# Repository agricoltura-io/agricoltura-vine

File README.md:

# agricoltura-vine
daisy chainable interface for a variety of sensors for various agriculture applications, this is Agricoltura-io's wired sense and control platform.

Quick Specs:
- ST Microelectronics STM32F446RET6 ARM Cortex M4F 180MHZ MCU
- 5V Tolerant Analog Inputs
- 8x I2C interfaces
- 4x UART interface (via mux)
- 8x 5V digital IO ports
- 2x G5LE-14 DC5 SPDT Relays
- USB 2.0 connectivity
- RS485 port
- 24VAC power input
- 2A 3.3V DCDC Regulator, for supporting lots of sensors
- 2A 5V DCDC Regulator, for 5V IO and other devices

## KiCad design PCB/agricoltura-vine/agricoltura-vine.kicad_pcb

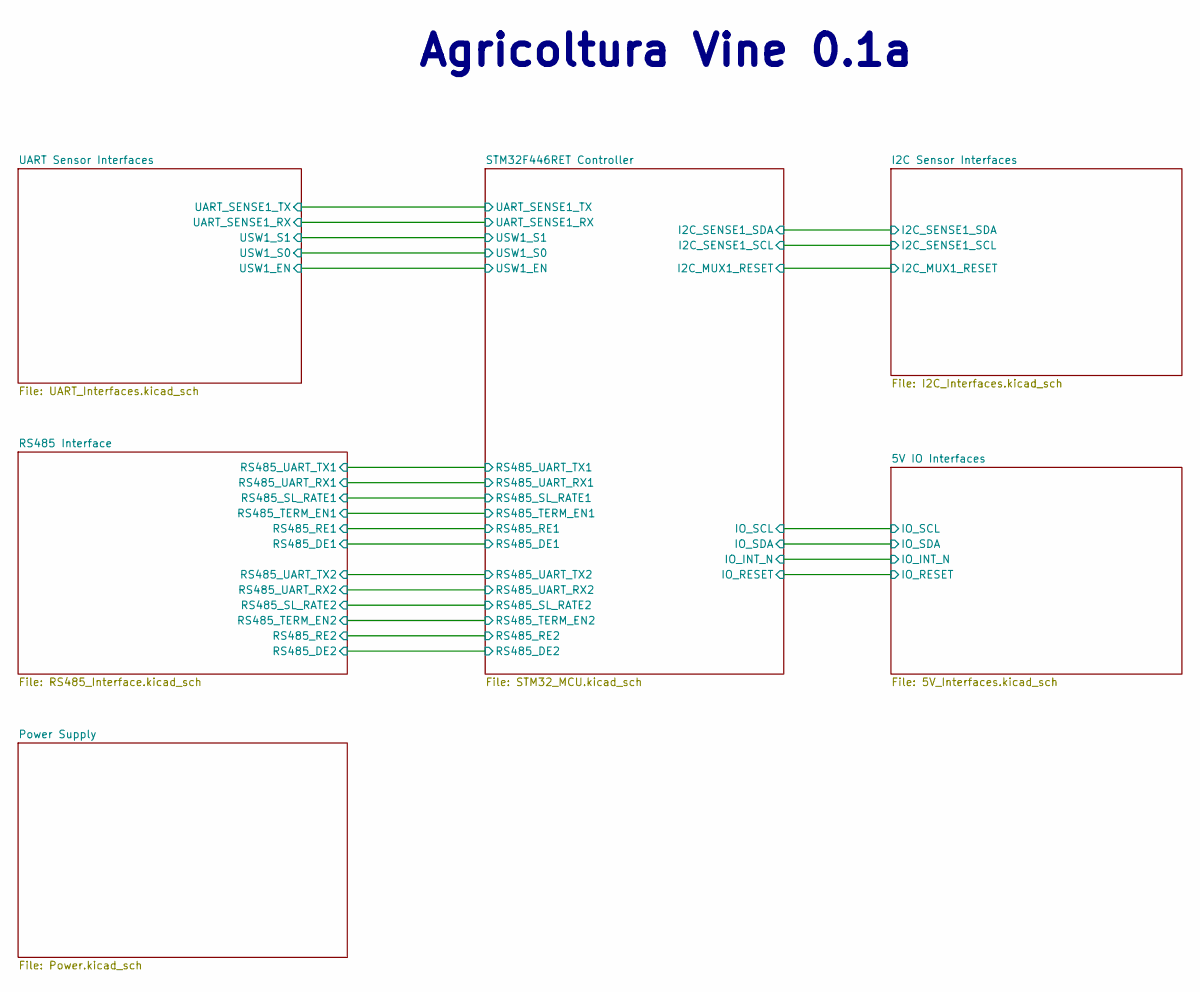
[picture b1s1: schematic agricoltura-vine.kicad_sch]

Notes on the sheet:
Agricoltura Vine 0.1a

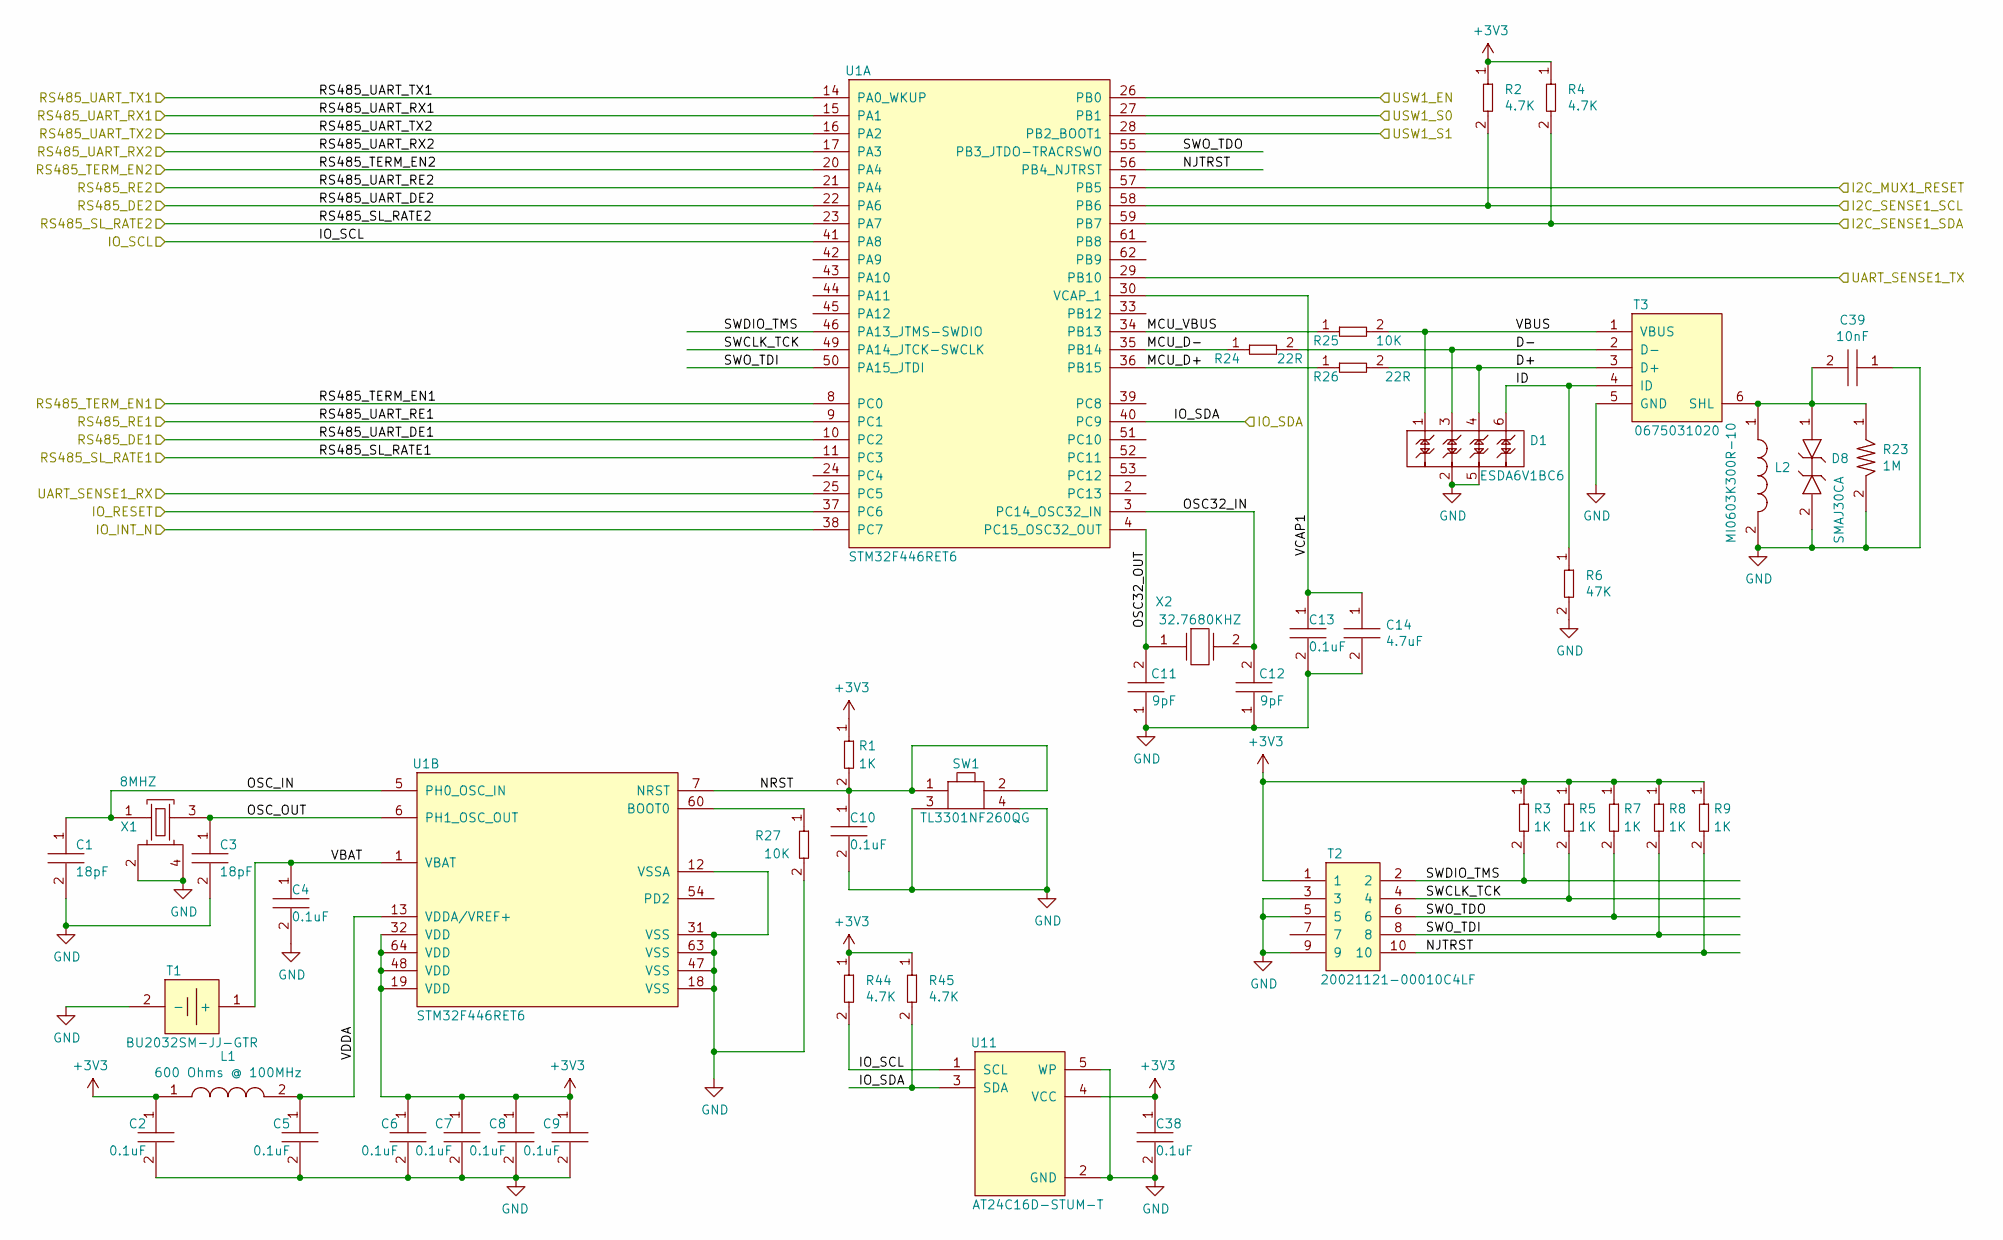
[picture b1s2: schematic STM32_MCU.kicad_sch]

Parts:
C1, C3: GCM1555C1H180GA16D; C0402; Tolerance 2%; Voltage 50V; MFR# GCM1555C1H180GA16D
C2, C4, C5, C6, C7, C8, C9, C10, C13, C38: C0402C104K9PACTU; R0402; Tolerance 10%; Voltage 6.3V; MFR# C0402C104K9PACTU
C11, C12: CL05C090CB5NNNC; C0402; Tolerance ±0.25pF; Voltage 50V; MFR# CL05C090CB5NNNC
C14: GRM155R60J475ME47D; C0402; Tolerance 20%; Voltage 6.3V; MFR# GRM155R60J475ME47D
C39: C0603X103K1RAC3316; C0603; Tolerance 10%; Voltage 100V; MFR# C0603X103K1RAC3316
D1: ESDA6V1BC6; SOT-23-6_Handsoldering; Tolerance *; Voltage 5V/6.1VBreakdown; MFR# ESDA6V1BC6
D8: SMAJ30CA; Tolerance *; Voltage 30V Clamp; MFR# SMAJ30CA
L1: BLM15HG601SN1D; Tolerance *; Voltage *; MFR# BLM15HG601SN1D
L2: MI0603K300R-10; Tolerance *; Voltage *; MFR# MI0603K300R-10
R1, R3, R5, R7, R8, R9: RC0402FR-071KL; R0402; Tolerance 1%; Voltage *; MFR# RC0402FR-071KL
R2, R4, R44, R45: RC0402FR-074K7L; R0402; Tolerance 1%; Voltage *; MFR# RC0402FR-074K7L
R6: RC0603FR-0747KL; R0603; Tolerance 1%; Voltage *; MFR# RC0603FR-0747KL
R23: RC1206FR-071ML; R1206; Tolerance 1%; Voltage *; MFR# RC1206FR-071ML
R24, R26: RC0402FR-0722RL; R0402; Tolerance 1%; Voltage *; MFR# RC0402FR-0722RL
R25, R27: RC0402FR-0710KL; R0402; Tolerance 1%; Voltage *; MFR# RC0402FR-0710KL
SW1: TL3301NF260QG; Tolerance *; Voltage 12VDC; MFR# TL3301NF260QG
T1: BU2032SM-JJ-GTR; Tolerance *; Voltage 3.3V; MFR# BU2032SM-JJ-GTR
T2: 20021121-00010C4LF; Tolerance *; Voltage *; MFR# 20021121-00010C4LF
T3: 0675031020; USB_Mini-B; Tolerance *; Voltage 5V; MFR# 0675031020
U1: STM32F446RET6; Tolerance *; Voltage 1.7V ~ 3.6V; MFR# STM32F446RET6
U11: AT24C16D-STUM-T; SOT-23-5; Tolerance *; Voltage 3.3V; MFR# AT24C16D-STUM-T
X1: ABM3B-8.000MHZ-B2-T; ABM3B8.000MHZB2T; Tolerance *; Voltage *; MFR# ABM3B-8.000MHZ-B2-T
X2: ABS07-32.768KHZ-9-T; Tolerance *; Voltage *; MFR# ABS07-32.768KHZ-9-T

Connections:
+3V3: C2.1, C6.1, C7.1, C8.1, C9.1, C38.1, L1.1, R1.1, R2.1, R3.1, R4.1, R5.1, R7.1, R8.1, R9.1, R44.1, R45.1, T2.1, U1.19 (VDD), U1.32 (VDD), U1.48 (VDD), U1.64 (VDD), U11.4 (VCC); also elsewhere on the board
/5V IO Interfaces/IO_INT_N: U1.38 (PC7); also elsewhere on the board
/5V IO Interfaces/IO_RESET: U1.37 (PC6); also elsewhere on the board
/5V IO Interfaces/IO_SCL: R44.2, U1.41 (PA8), U11.1 (SCL); also elsewhere on the board
/5V IO Interfaces/IO_SDA: R45.2, U1.40 (PC9), U11.3 (SDA); also elsewhere on the board
/I2C Sensor Interfaces/I2C_MUX1_RESET: U1.57 (PB5); also elsewhere on the board
/I2C Sensor Interfaces/I2C_SENSE1_SCL: R2.2, U1.58 (PB6); also elsewhere on the board
/I2C Sensor Interfaces/I2C_SENSE1_SDA: R4.2, U1.59 (PB7); also elsewhere on the board
/RS485 Interface/RS485_DE1: U1.10 (PC2); also elsewhere on the board
/RS485 Interface/RS485_DE2: U1.22 (PA6); also elsewhere on the board
/RS485 Interface/RS485_RE1: U1.9 (PC1); also elsewhere on the board
/RS485 Interface/RS485_RE2: U1.21 (PA4); also elsewhere on the board
/RS485 Interface/RS485_SL_RATE1: U1.11 (PC3); also elsewhere on the board
/RS485 Interface/RS485_SL_RATE2: U1.23 (PA7); also elsewhere on the board
/RS485 Interface/RS485_TERM_EN1: U1.8 (PC0); also elsewhere on the board
/RS485 Interface/RS485_TERM_EN2: U1.20 (PA4); also elsewhere on the board
/RS485 Interface/RS485_UART_RX1: U1.15 (PA1); also elsewhere on the board
/RS485 Interface/RS485_UART_RX2: U1.17 (PA3); also elsewhere on the board
/RS485 Interface/RS485_UART_TX1: U1.14 (PA0_WKUP); also elsewhere on the board
/RS485 Interface/RS485_UART_TX2: U1.16 (PA2); also elsewhere on the board
/STM32F446RET Controller/D+: D1.4, R26.2, T3.3 (D+)
/STM32F446RET Controller/D-: D1.3, R24.2, T3.2 (D-)
/STM32F446RET Controller/ID: D1.6, R6.1, T3.4 (ID)
/STM32F446RET Controller/MCU_D+: R26.1, U1.36 (PB15)
/STM32F446RET Controller/MCU_D-: R24.1, U1.35 (PB14)
/STM32F446RET Controller/MCU_VBUS: R25.1, U1.34 (PB13)
/STM32F446RET Controller/NJTRST: R9.2, T2.10, U1.56 (PB4_NJTRST)
/STM32F446RET Controller/NRST: C10.1, R1.2, SW1.1, SW1.2, U1.7 (NRST)
/STM32F446RET Controller/OSC32_IN: C12.2, U1.3 (PC14_OSC32_IN), X2.2
/STM32F446RET Controller/OSC32_OUT: C11.2, U1.4 (PC15_OSC32_OUT), X2.1
/STM32F446RET Controller/OSC_IN: C1.1, U1.5 (PH0_OSC_IN), X1.1
/STM32F446RET Controller/OSC_OUT: C3.1, U1.6 (PH1_OSC_OUT), X1.3
/STM32F446RET Controller/SWCLK_TCK: R5.2, T2.4, U1.49 (PA14_JTCK-SWCLK)
/STM32F446RET Controller/SWDIO_TMS: R3.2, T2.2, U1.46 (PA13_JTMS-SWDIO)
/STM32F446RET Controller/SWO_TDI: R8.2, T2.8, U1.50 (PA15_JTDI)
/STM32F446RET Controller/SWO_TDO: R7.2, T2.6, U1.55 (PB3_JTDO-TRACRSWO)
/STM32F446RET Controller/UART_SENSE1_RX: U1.25 (PC5); also elsewhere on the board
/STM32F446RET Controller/UART_SENSE1_TX: U1.29 (PB10); also elsewhere on the board
/STM32F446RET Controller/USW1_EN: U1.26 (PB0); also elsewhere on the board
/STM32F446RET Controller/USW1_S0: U1.27 (PB1); also elsewhere on the board
/STM32F446RET Controller/USW1_S1: U1.28 (PB2_BOOT1); also elsewhere on the board
/STM32F446RET Controller/VBAT: C4.1, T1.1 (+), U1.1 (VBAT)
/STM32F446RET Controller/VBUS: D1.1, R25.2, T3.1 (VBUS)
/STM32F446RET Controller/VCAP1: C13.1, C14.1, U1.30 (VCAP_1)
/STM32F446RET Controller/VDDA: C5.1, L1.2, U1.13 (VDDA/VREF+)
GND: C1.2, C2.2, C3.2, C4.2, C5.2, C6.2, C7.2, C8.2, C9.2, C10.2, C11.1, C12.1, C13.2, C14.2, C38.2, C39.1, D1.2, D1.5, D8.2, L2.2, R6.2, R23.2, R27.2, SW1.3, SW1.4, T1.2 (-), T2.3, T2.5, T2.9, T3.5 (GND), U1.12 (VSSA), U1.18 (VSS), U1.31 (VSS), U1.47 (VSS), U1.63 (VSS), U11.2 (GND), U11.5 (WP), X1.2, X1.4; also elsewhere on the board
unnamed: C39.2, D8.1, L2.1, R23.1, T3.6 (SHL)
unnamed: R27.1, U1.60 (BOOT0)

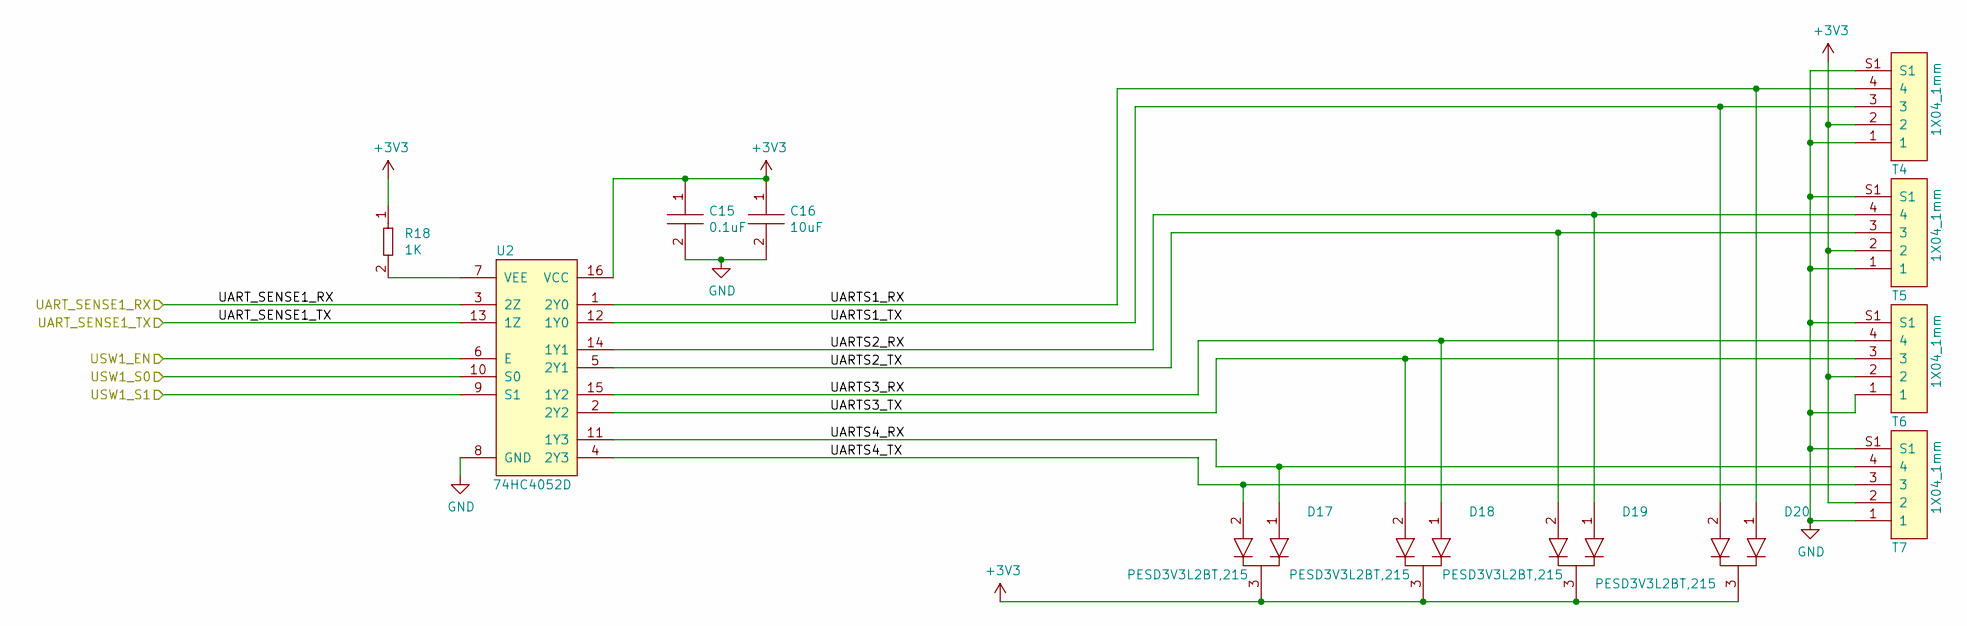
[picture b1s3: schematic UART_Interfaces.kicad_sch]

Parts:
C15: C0402C104K9PACTU; R0402; Tolerance 10%; Voltage 6.3V; MFR# C0402C104K9PACTU
C16: GRM188R61A106KE69J; C0603; Tolerance 10%; Voltage 10V; MFR# GRM188R61A106KE69J
D17, D18, D19, D20: PESD3V3L2BT,215; SOT-23; Tolerance *; Voltage *; MFR# PESD3V3L2BT,215
R18: RC0402FR-071KL; R0402; Tolerance 1%; Voltage *; MFR# RC0402FR-071KL
T4, T5, T6, T7: BM04B-SRSS-TB(LF)(SN); CONN_BM04B-SRSS-TB(LF)(SN); Tolerance *; Voltage 50V; MFR# BM04B-SRSS-TB(LF)(SN)
U2: 74HC4052D; Tolerance *; Voltage 2V ~ 6V; MFR# 74HC4052D

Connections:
+3V3: C15.1, C16.1, D17.3, D18.3, D19.3, D20.3, R18.1, T4.2, T5.2, T6.2, T7.2, U2.16 (VCC); also elsewhere on the board
/STM32F446RET Controller/UART_SENSE1_RX: U2.3 (2Z); also elsewhere on the board
/STM32F446RET Controller/UART_SENSE1_TX: U2.13 (1Z); also elsewhere on the board
/STM32F446RET Controller/USW1_EN: U2.6 (E); also elsewhere on the board
/STM32F446RET Controller/USW1_S0: U2.10 (S0); also elsewhere on the board
/STM32F446RET Controller/USW1_S1: U2.9 (S1); also elsewhere on the board
/UART Sensor Interfaces/UARTS1_RX: D20.1, T4.4, U2.1 (2Y0)
/UART Sensor Interfaces/UARTS1_TX: D20.2, T4.3, U2.12 (1Y0)
/UART Sensor Interfaces/UARTS2_RX: D19.1, T5.4, U2.14 (1Y1)
/UART Sensor Interfaces/UARTS2_TX: D19.2, T5.3, U2.5 (2Y1)
/UART Sensor Interfaces/UARTS3_RX: D18.1, T6.4, U2.15 (1Y2)
/UART Sensor Interfaces/UARTS3_TX: D18.2, T6.3, U2.2 (2Y2)
/UART Sensor Interfaces/UARTS4_RX: D17.1, T7.4, U2.11 (1Y3)
/UART Sensor Interfaces/UARTS4_TX: D17.2, T7.3, U2.4 (2Y3)
GND: C15.2, C16.2, T4.1, T4.S1, T5.1, T5.S1, T6.1, T6.S1, T7.1, T7.S1, U2.8 (GND); also elsewhere on the board
unnamed: R18.2, U2.7 (VEE)

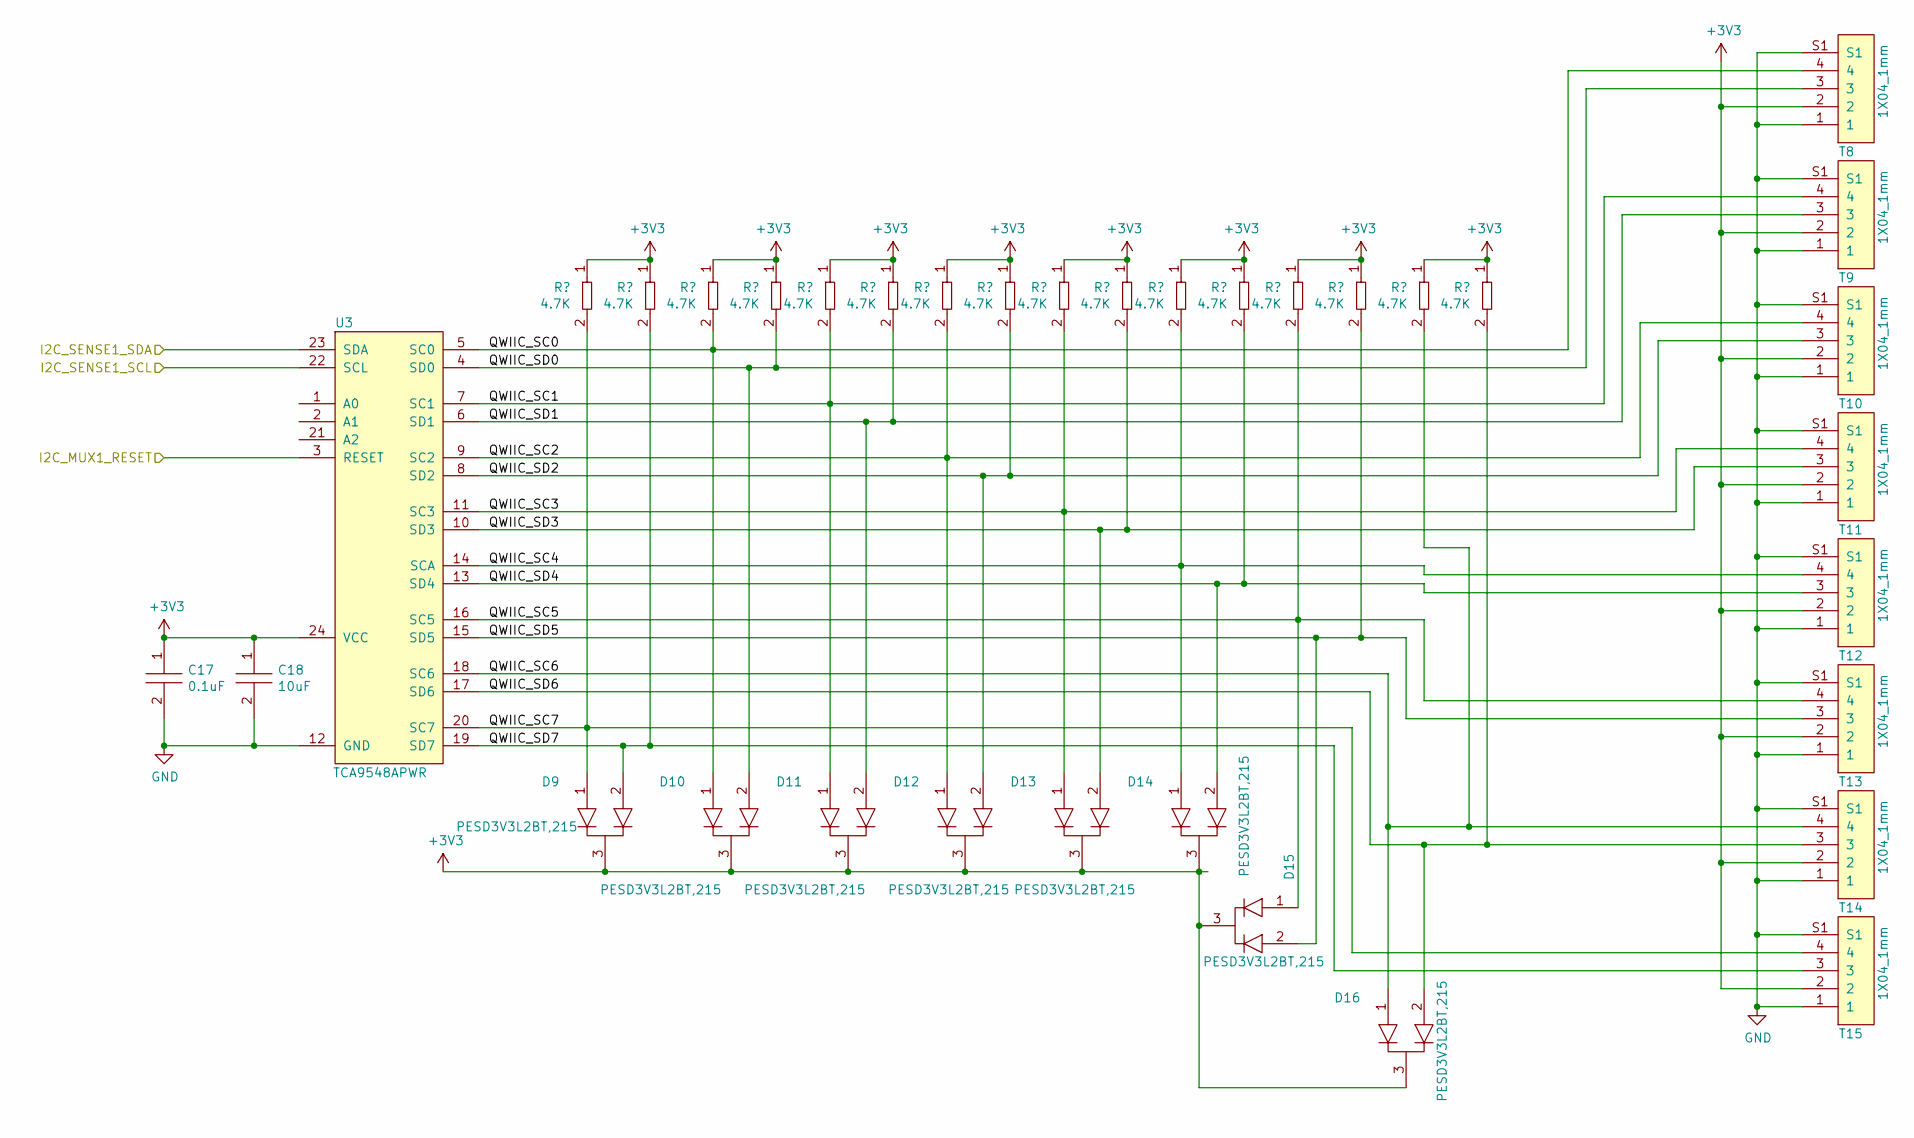
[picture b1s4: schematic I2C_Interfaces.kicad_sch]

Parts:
C17: C0402C104K9PACTU; R0402; Tolerance 10%; Voltage 6.3V; MFR# C0402C104K9PACTU
C18: GRM188R61A106KE69J; C0603; Tolerance 10%; Voltage 10V; MFR# GRM188R61A106KE69J
D9, D10, D11, D12, D13, D14, D15, D16: PESD3V3L2BT,215; SOT-23; Tolerance *; Voltage *; MFR# PESD3V3L2BT,215
R28, R29, R30, R31, R32, R33, R34, R35, R36, R37, R38, R39, R40, R41, R42, R43: RC0402FR-074K7L; R0402; Tolerance 1%; Voltage *; MFR# RC0402FR-074K7L
T8, T9, T10, T11, T12, T13, T14, T15: BM04B-SRSS-TB(LF)(SN); CONN_BM04B-SRSS-TB(LF)(SN); Tolerance *; Voltage 50V; MFR# BM04B-SRSS-TB(LF)(SN)
U3: TCA9548APWR; Tolerance *; Voltage 1.65V ~ 5.5V; MFR# TCA9548APWR

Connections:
+3V3: C17.1, C18.1, D9.3, D10.3, D11.3, D12.3, D13.3, D14.3, D15.3, D16.3, R28.1, R29.1, R30.1, R31.1, R32.1, R33.1, R34.1, R35.1, R36.1, R37.1, R38.1, R39.1, R40.1, R41.1, R42.1, R43.1, T8.2, T9.2, T10.2, T11.2, T12.2, T13.2, T14.2, T15.2, U3.24 (VCC); also elsewhere on the board
/I2C Sensor Interfaces/I2C_MUX1_RESET: U3.3 (RESET); also elsewhere on the board
/I2C Sensor Interfaces/I2C_SENSE1_SCL: U3.22 (SCL); also elsewhere on the board
/I2C Sensor Interfaces/I2C_SENSE1_SDA: U3.23 (SDA); also elsewhere on the board
/I2C Sensor Interfaces/QWIIC_SC0: D10.1, R30.2, T8.4, U3.5 (SC0)
/I2C Sensor Interfaces/QWIIC_SC1: D11.1, R32.2, T9.4, U3.7 (SC1)
/I2C Sensor Interfaces/QWIIC_SC2: D12.1, R34.2, T10.4, U3.9 (SC2)
/I2C Sensor Interfaces/QWIIC_SC3: D13.1, R36.2, T11.4, U3.11 (SC3)
/I2C Sensor Interfaces/QWIIC_SC4: D14.1, R38.2, T12.4, U3.14 (SCA)
/I2C Sensor Interfaces/QWIIC_SC5: D15.1, R40.2, T13.4, U3.16 (SC5)
/I2C Sensor Interfaces/QWIIC_SC6: D16.1, R42.2, T14.4, U3.18 (SC6)
/I2C Sensor Interfaces/QWIIC_SC7: D9.1, R28.2, T15.4, U3.20 (SC7)
/I2C Sensor Interfaces/QWIIC_SD0: D10.2, R31.2, T8.3, U3.4 (SD0)
/I2C Sensor Interfaces/QWIIC_SD1: D11.2, R33.2, T9.3, U3.6 (SD1)
/I2C Sensor Interfaces/QWIIC_SD2: D12.2, R35.2, T10.3, U3.8 (SD2)
/I2C Sensor Interfaces/QWIIC_SD3: D13.2, R37.2, T11.3, U3.10 (SD3)
/I2C Sensor Interfaces/QWIIC_SD4: D14.2, R39.2, T12.3, U3.13 (SD4)
/I2C Sensor Interfaces/QWIIC_SD5: D15.2, R41.2, T13.3, U3.15 (SD5)
/I2C Sensor Interfaces/QWIIC_SD6: D16.2, R43.2, T14.3, U3.17 (SD6)
/I2C Sensor Interfaces/QWIIC_SD7: D9.2, R29.2, T15.3, U3.19 (SD7)
GND: C17.2, C18.2, T8.1, T8.S1, T9.1, T9.S1, T10.1, T10.S1, T11.1, T11.S1, T12.1, T12.S1, T13.1, T13.S1, T14.1, T14.S1, T15.1, T15.S1, U3.12 (GND); also elsewhere on the board

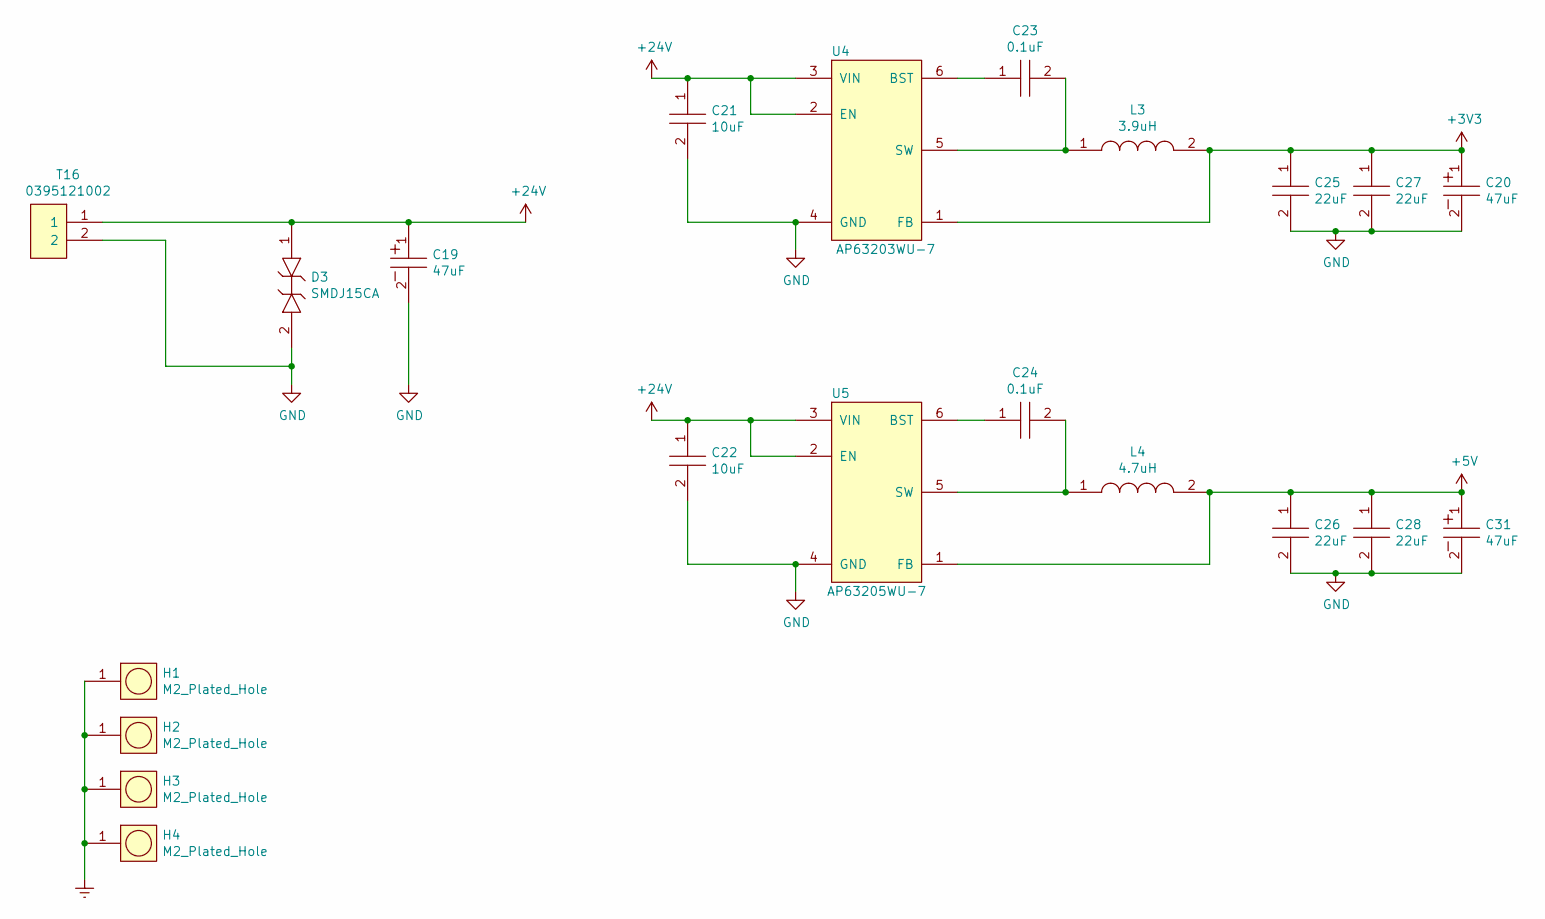
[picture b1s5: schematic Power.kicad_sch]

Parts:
C19: UUQ1H470MCL1GS; CP_Elec_8x10; Tolerance 20%; Voltage 50V; MFR# UUQ1H470MCL1GS
C20, C31: UCM1C470MCL1GS; Tolerance 20%; Voltage 16V; MFR# UCM1C470MCL1GS
C21, C22: GRT31CR61H106KE01L; C1206; Tolerance 10%; Voltage 50V; MFR# GRT31CR61H106KE01L
C23: C0805C104M5RACTU; C0805; Tolerance 20%; Voltage 50V; MFR# C0805C104M5RACTU
C24: C2012X7R2A104K125AA; C0805; Tolerance 10%; Voltage 100V; MFR# C2012X7R2A104K125AA
C25, C27: GRM21BD70J226ME44L; C0805; Tolerance 20%; Voltage 6.3v; MFR# GRM21BD70J226ME44L
C26, C28: GRT31CC81C226KE01L; C1206; Tolerance 10%; Voltage 16V; MFR# GRT31CC81C226KE01L
D3: SMDJ15CA; Tolerance *; Voltage 24V Clamp; MFR# SMDJ15CA
H1, H2, H3, H4: M2_Plated_Hole; M2_HOLE; Tolerance *; Voltage *; MFR# *
L3: ASPI-0628-3R9M-T1; Tolerance 20%; Voltage *; MFR# ASPI-0628-3R9M-T1
L4: SRP6540-4R7M; Tolerance 20%; Voltage *; MFR# SRP6540-4R7M
T16: 0395121002; Tolerance *; Voltage 300V; MFR# 0395121002
U4: AP63203WU-7; SOT-23-6_Handsoldering; Tolerance *; Voltage 32V, 3.3V; MFR# AP63203WU-7
U5: AP63205WU-7; SOT-23-6_Handsoldering; Tolerance *; Voltage 32V, 5V; MFR# AP63205WU-7

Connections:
+3V3: C20.1, C25.1, C27.1, L3.2, U4.1 (FB); also elsewhere on the board
+5V: C26.1, C28.1, C31.1, L4.2, U5.1 (FB); also elsewhere on the board
+24V: C19.1, C21.1, C22.1, D3.1, T16.1, U4.2 (EN), U4.3 (VIN), U5.2 (EN), U5.3 (VIN)
Earth: H1.1, H2.1, H3.1, H4.1
GND: C19.2, C20.2, C21.2, C22.2, C25.2, C26.2, C27.2, C28.2, C31.2, D3.2, T16.2, U4.4 (GND), U5.4 (GND); also elsewhere on the board
unnamed: C23.1, U4.6 (BST)
unnamed: C23.2, L3.1, U4.5 (SW)
unnamed: C24.1, U5.6 (BST)
unnamed: C24.2, L4.1, U5.5 (SW)

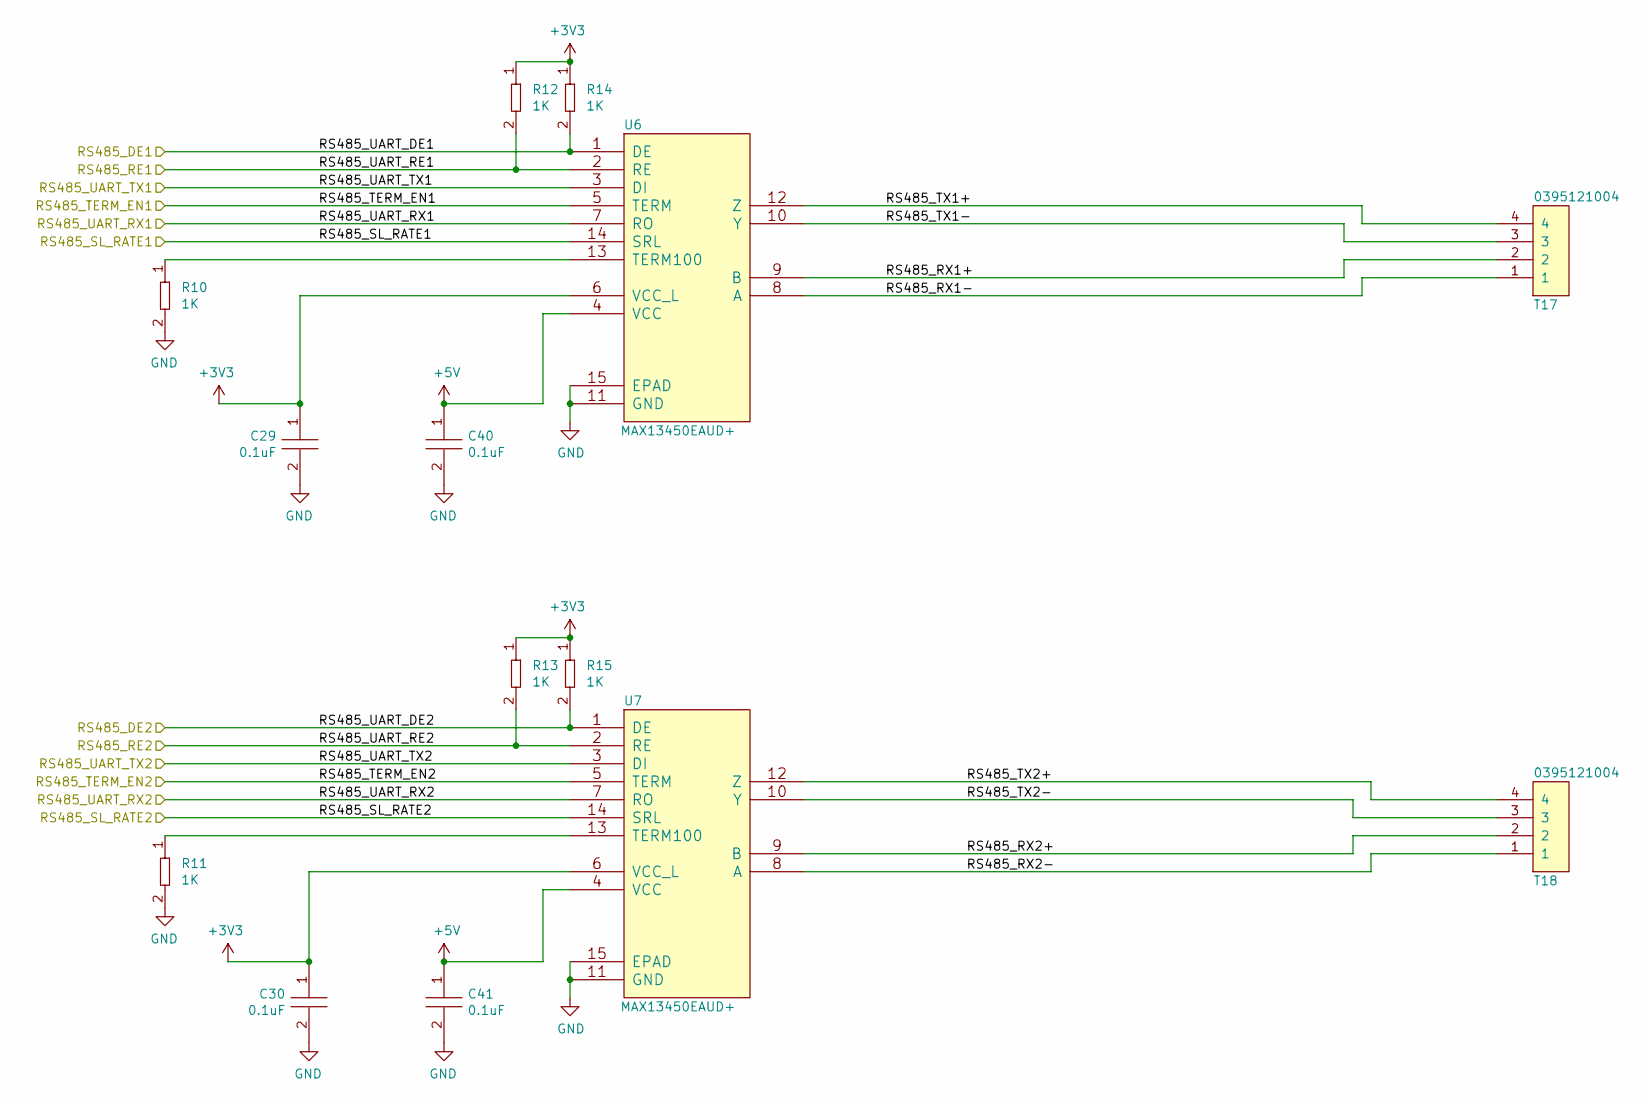
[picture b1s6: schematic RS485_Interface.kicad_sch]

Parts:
C29, C30: C0402C104K9PACTU; R0402; Tolerance 10%; Voltage 6.3V; MFR# C0402C104K9PACTU
C40, C41: CGA3E2X7R1H104K080AA; C0603; Tolerance 10%; Voltage 50V; MFR# CGA3E2X7R1H104K080AA
R10, R11, R12, R13, R14, R15: RC0402FR-071KL; R0402; Tolerance 1%; Voltage *; MFR# RC0402FR-071KL
T17, T18: 0395121004; Tolerance *; Voltage 300V; MFR# 0395121004
U6, U7: MAX13450EAUD+; MAX13450EAUD&plus_; Tolerance *; Voltage 4.75V ~ 5.25V; MFR# MAX13450EAUD+

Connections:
+3V3: C29.1, C30.1, R12.1, R13.1, R14.1, R15.1, U6.6 (VCC_L), U7.6 (VCC_L); also elsewhere on the board
+5V: C40.1, C41.1, U6.4 (VCC), U7.4 (VCC); also elsewhere on the board
/RS485 Interface/RS485_DE1: R14.2, U6.1 (DE); also elsewhere on the board
/RS485 Interface/RS485_DE2: R15.2, U7.1 (DE); also elsewhere on the board
/RS485 Interface/RS485_RE1: R12.2, U6.2 (RE); also elsewhere on the board
/RS485 Interface/RS485_RE2: R13.2, U7.2 (RE); also elsewhere on the board
/RS485 Interface/RS485_RX1+: T17.2, U6.9 (B)
/RS485 Interface/RS485_RX1-: T17.1, U6.8 (A)
/RS485 Interface/RS485_RX2+: T18.2, U7.9 (B)
/RS485 Interface/RS485_RX2-: T18.1, U7.8 (A)
/RS485 Interface/RS485_SL_RATE1: U6.14 (SRL); also elsewhere on the board
/RS485 Interface/RS485_SL_RATE2: U7.14 (SRL); also elsewhere on the board
/RS485 Interface/RS485_TERM_EN1: U6.5 (TERM); also elsewhere on the board
/RS485 Interface/RS485_TERM_EN2: U7.5 (TERM); also elsewhere on the board
/RS485 Interface/RS485_TX1+: T17.4, U6.12 (Z)
/RS485 Interface/RS485_TX1-: T17.3, U6.10 (Y)
/RS485 Interface/RS485_TX2+: T18.4, U7.12 (Z)
/RS485 Interface/RS485_TX2-: T18.3, U7.10 (Y)
/RS485 Interface/RS485_UART_RX1: U6.7 (RO); also elsewhere on the board
/RS485 Interface/RS485_UART_RX2: U7.7 (RO); also elsewhere on the board
/RS485 Interface/RS485_UART_TX1: U6.3 (DI); also elsewhere on the board
/RS485 Interface/RS485_UART_TX2: U7.3 (DI); also elsewhere on the board
GND: C29.2, C30.2, C40.2, C41.2, R10.2, R11.2, U6.11 (GND), U6.15 (EPAD), U7.11 (GND), U7.15 (EPAD); also elsewhere on the board
unnamed: R10.1, U6.13 (TERM100)
unnamed: R11.1, U7.13 (TERM100)

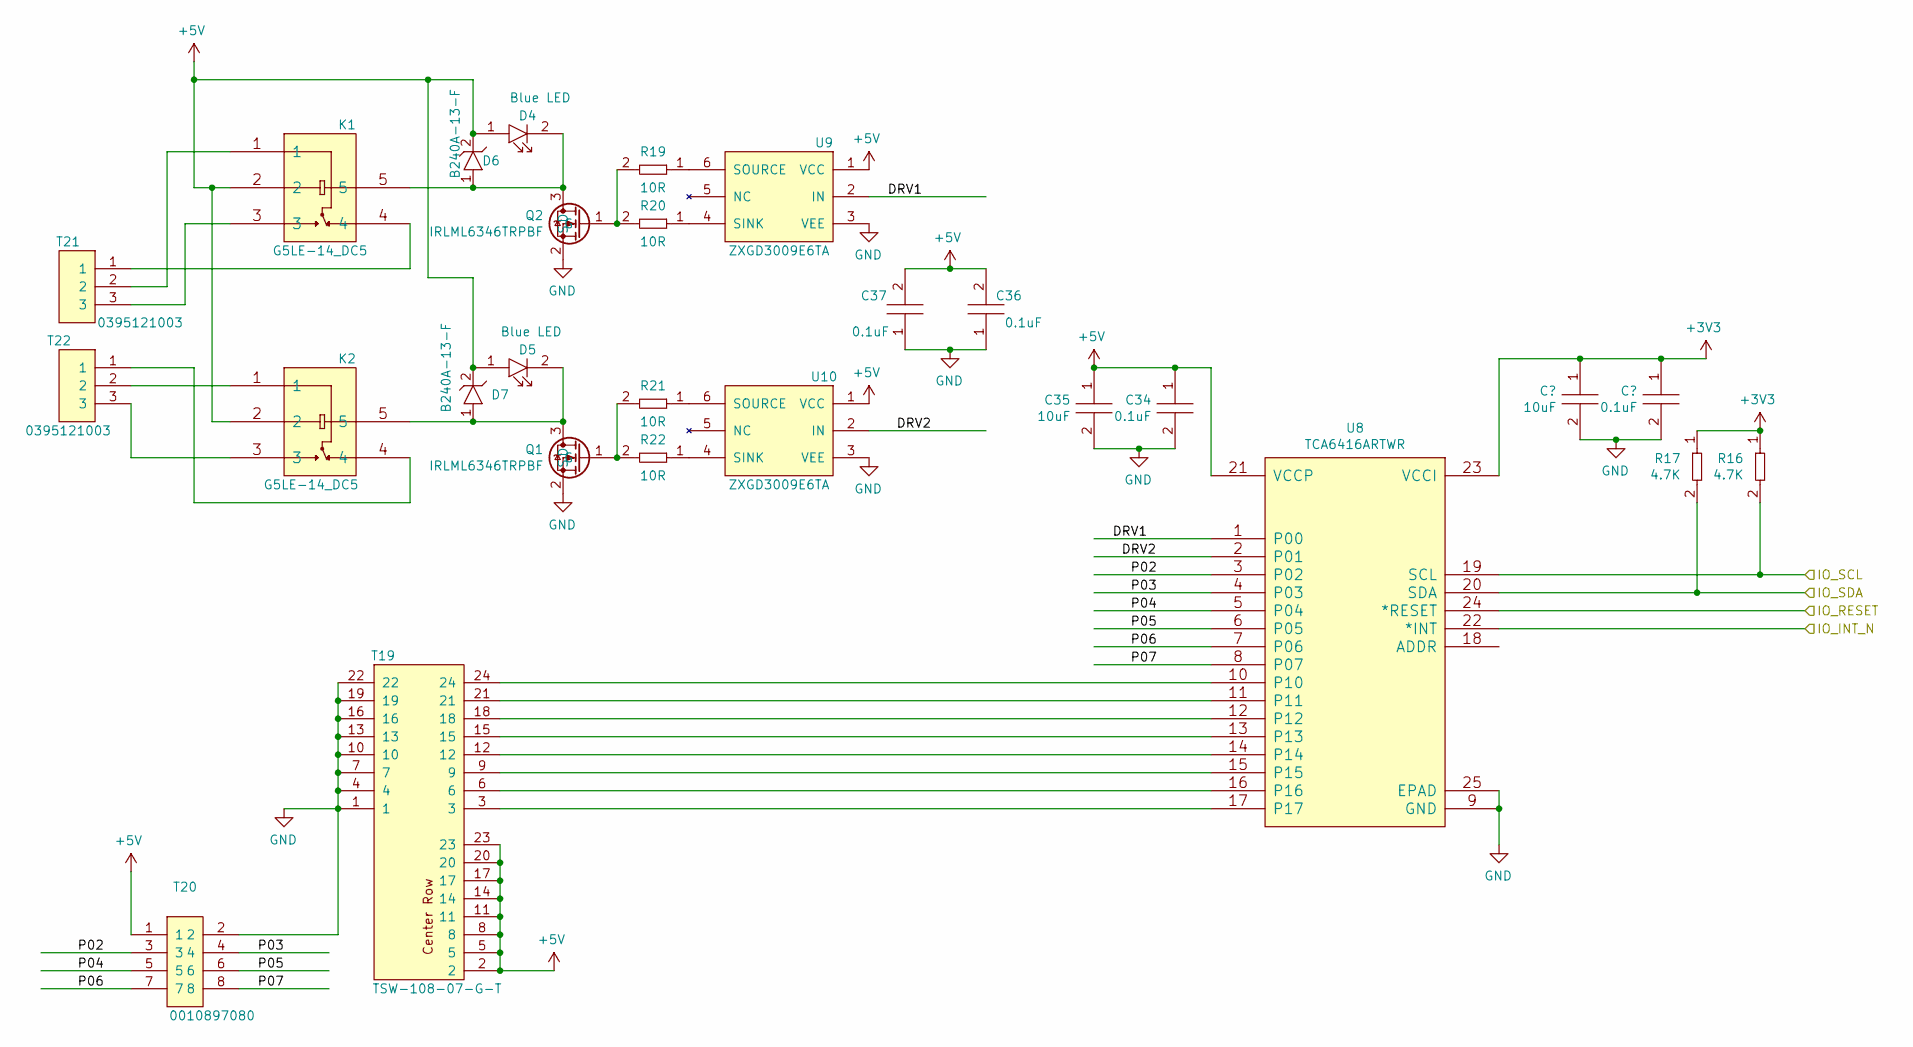
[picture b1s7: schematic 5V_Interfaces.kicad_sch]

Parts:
C32, C34, C36, C37: C0402C104K9PACTU; R0402; Tolerance 10%; Voltage 6.3V; MFR# C0402C104K9PACTU
C33, C35: GRM188R61A106KE69J; C0603; Tolerance 10%; Voltage 10V; MFR# GRM188R61A106KE69J
D4, D5: LTST-C194TBKT; LED0603; Tolerance *; Voltage 3.3V; MFR# LTST-C194TBKT
D6, D7: B240A-13-F; Tolerance *; Voltage 40V; MFR# B240A-13-F
K1, K2: G5LE-14_DC5; Tolerance *; Voltage 5VDC Coil, 250VAC, 125VDC - Max; MFR# G5LE-14 DC5
Q1, Q2: IRLML6346TRPBF; SOT-23; Tolerance *; Voltage 30V; MFR# IRLML6346TRPBF
R16, R17: RC0402FR-074K7L; R0402; Tolerance 1%; Voltage *; MFR# RC0402FR-074K7L
R19, R20, R21, R22: RC0402FR-0710RL; R0402; Tolerance 1%; Voltage *; MFR# RC0402FR-0710RL
T19: TSW-108-07-G-T; Tolerance *; Voltage *; MFR# TSW-108-07-G-T
T20: 0010897080; Pin_Header_Straight_2x04_Pitch2.54mm; Tolerance *; Voltage *; MFR# 0010897080
T21, T22: 0395121003; Tolerance *; Voltage 300V; MFR# 0395121003
U8: TCA6416ARTWR; Tolerance *; Voltage 1.65V ~ 5.5V; MFR# TCA6416ARTWR
U9, U10: ZXGD3009E6TA; SOT-23-6_Handsoldering; Tolerance *; Voltage 40V; MFR# ZXGD3009E6TA

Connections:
+3V3: C32.1, C33.1, R16.1, R17.1, U8.23 (VCCI); also elsewhere on the board
+5V: C34.1, C35.1, C36.2, C37.2, D4.1, D5.1, D6.2, D7.2, K1.2, K2.2, T19.2, T19.5, T19.8, T19.11, T19.14, T19.17, T19.20, T19.23, T20.1, U8.21 (VCCP), U9.1 (VCC), U10.1 (VCC); also elsewhere on the board
/5V IO Interfaces/DRV1: U8.1 (P00), U9.2 (IN)
/5V IO Interfaces/DRV2: U8.2 (P01), U10.2 (IN)
/5V IO Interfaces/IO_INT_N: U8.22 (*INT); also elsewhere on the board
/5V IO Interfaces/IO_RESET: U8.24 (*RESET); also elsewhere on the board
/5V IO Interfaces/IO_SCL: R16.2, U8.19 (SCL); also elsewhere on the board
/5V IO Interfaces/IO_SDA: R17.2, U8.20 (SDA); also elsewhere on the board
/5V IO Interfaces/P02: T20.3, U8.3 (P02)
/5V IO Interfaces/P03: T20.4, U8.4 (P03)
/5V IO Interfaces/P04: T20.5, U8.5 (P04)
/5V IO Interfaces/P05: T20.6, U8.6 (P05)
/5V IO Interfaces/P06: T20.7, U8.7 (P06)
/5V IO Interfaces/P07: T20.8, U8.8 (P07)
GND: C32.2, C33.2, C34.2, C35.2, C36.1, C37.1, Q1.2 (S), Q2.2 (S), T19.1, T19.4, T19.7, T19.10, T19.13, T19.16, T19.19, T19.22, T20.2, U8.9 (GND), U8.25 (EPAD), U9.3 (VEE), U10.3 (VEE); also elsewhere on the board
unnamed: D4.2, D6.1, K1.5, Q2.3 (D)
unnamed: D5.2, D7.1, K2.5, Q1.3 (D)
unnamed: K1.1, T21.2
unnamed: K1.3, T21.3
unnamed: K1.4, T21.1
unnamed: K2.1, T22.2
unnamed: K2.3, T22.3
unnamed: K2.4, T22.1
unnamed: Q1.1 (G), R21.2, R22.2
unnamed: Q2.1 (G), R19.2, R20.2
unnamed: R19.1, U9.6 (SOURCE)
unnamed: R20.1, U9.4 (SINK)
unnamed: R21.1, U10.6 (SOURCE)
unnamed: R22.1, U10.4 (SINK)
unnamed: T19.3, U8.17
unnamed: T19.6, U8.16
unnamed: T19.9, U8.15
unnamed: T19.12, U8.14
unnamed: T19.15, U8.13
unnamed: T19.18, U8.12
unnamed: T19.21, U8.11
unnamed: T19.24, U8.10

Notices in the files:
parts and their libraries:
Copyright 2016 Accelerated Designs. All rights reserved.
